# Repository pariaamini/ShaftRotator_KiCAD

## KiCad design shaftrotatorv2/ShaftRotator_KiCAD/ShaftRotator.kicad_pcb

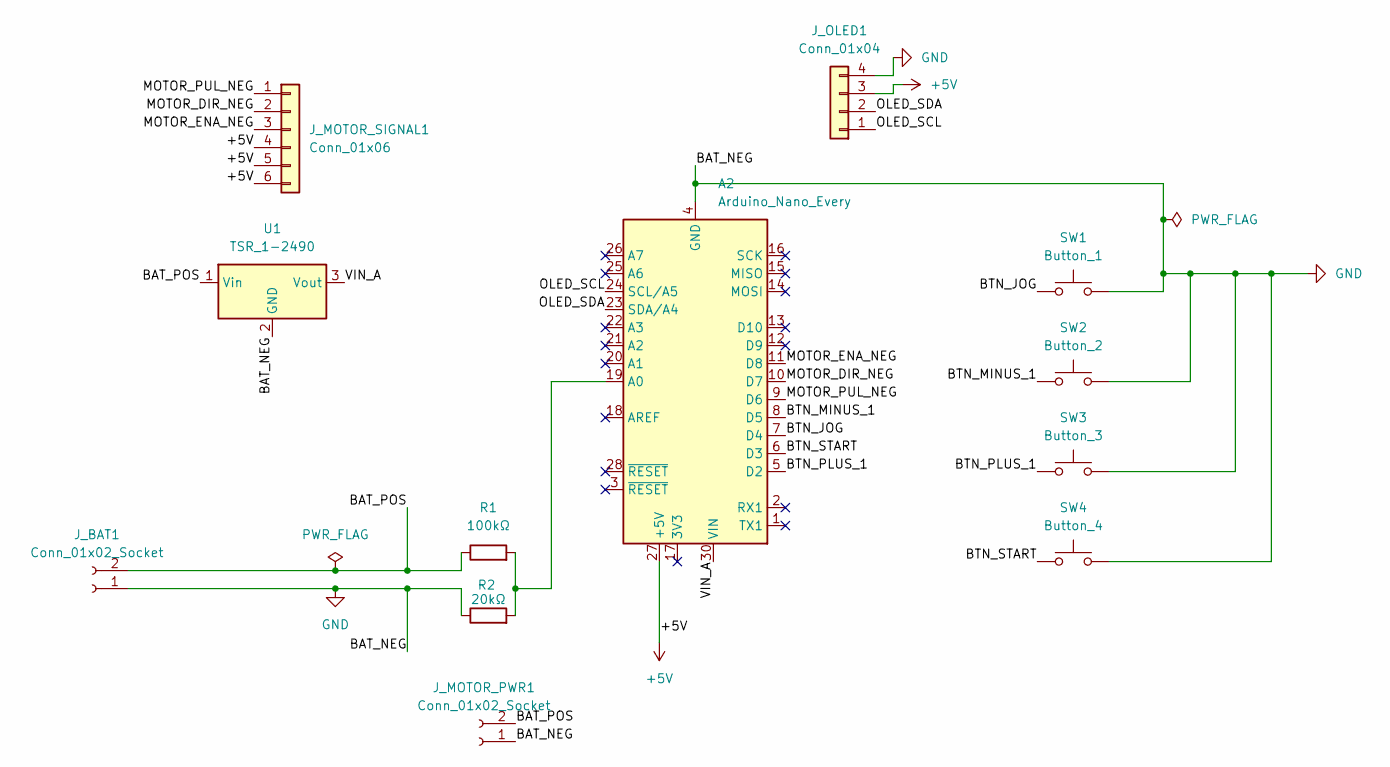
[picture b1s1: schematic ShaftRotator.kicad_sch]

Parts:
A2: Arduino_Nano_Every; Arduino_Nano
J_BAT1: Conn_01x02_Socket; JST_VH_B2P-VH_1x02_P3.96mm_Vertical
J_MOTOR_PWR1: Conn_01x02_Socket; JST_VH_B2P-VH_1x02_P3.96mm_Vertical
J_MOTOR_SIGNAL1: Conn_01x06; JST_PH_B6B-PH-K_1x06_P2.00mm_Vertical
J_OLED1: Conn_01x04; GROVE-HW4-2.0-90D
R1: 100kΩ; R_Axial_DIN0207_L6.3mm_D2.5mm_P10.16mm_Horizontal
R2: 20kΩ; R_Axial_DIN0207_L6.3mm_D2.5mm_P10.16mm_Horizontal
SW1: Button_1; SW_D6R90_F2_LFS
SW2: Button_2; SW_D6R90_F2_LFS
SW3: Button_3; SW_D6R90_F2_LFS
SW4: Button_4; SW_D6R90_F2_LFS
U1: TSR_1-2490; Converter_DCDC_TRACO_TSR-1_THT

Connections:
+5V: A2.27 (+5V), J_MOTOR_SIGNAL1.4, J_MOTOR_SIGNAL1.5, J_MOTOR_SIGNAL1.6, J_OLED1.3
/BAT_POS: J_BAT1.2, J_MOTOR_PWR1.2, R1.1, U1.1 (Vin)
/BTN_JOG: A2.7 (D4), SW1.1
/BTN_MINUS_1: A2.8 (D5), SW2.1
/BTN_PLUS_1: A2.5 (D2), SW3.1
/BTN_START: A2.6 (D3), SW4.1
/MOTOR_DIR_NEG: A2.10 (D7), J_MOTOR_SIGNAL1.2
/MOTOR_ENA_NEG: A2.11 (D8), J_MOTOR_SIGNAL1.3
/MOTOR_PUL_NEG: A2.9 (D6), J_MOTOR_SIGNAL1.1
/OLED_SCL: A2.24 (SCL/A5), J_OLED1.1
/OLED_SDA: A2.23 (SDA/A4), J_OLED1.2
/VIN_A: A2.30 (VIN), U1.3 (Vout)
GND: A2.4 (GND), A2.29 (GND), J_BAT1.1, J_MOTOR_PWR1.1, J_OLED1.4, R2.1, SW1.2, SW2.2, SW3.2, SW4.2, U1.2 (GND)
unnamed: A2.19 (A0), R1.2, R2.2

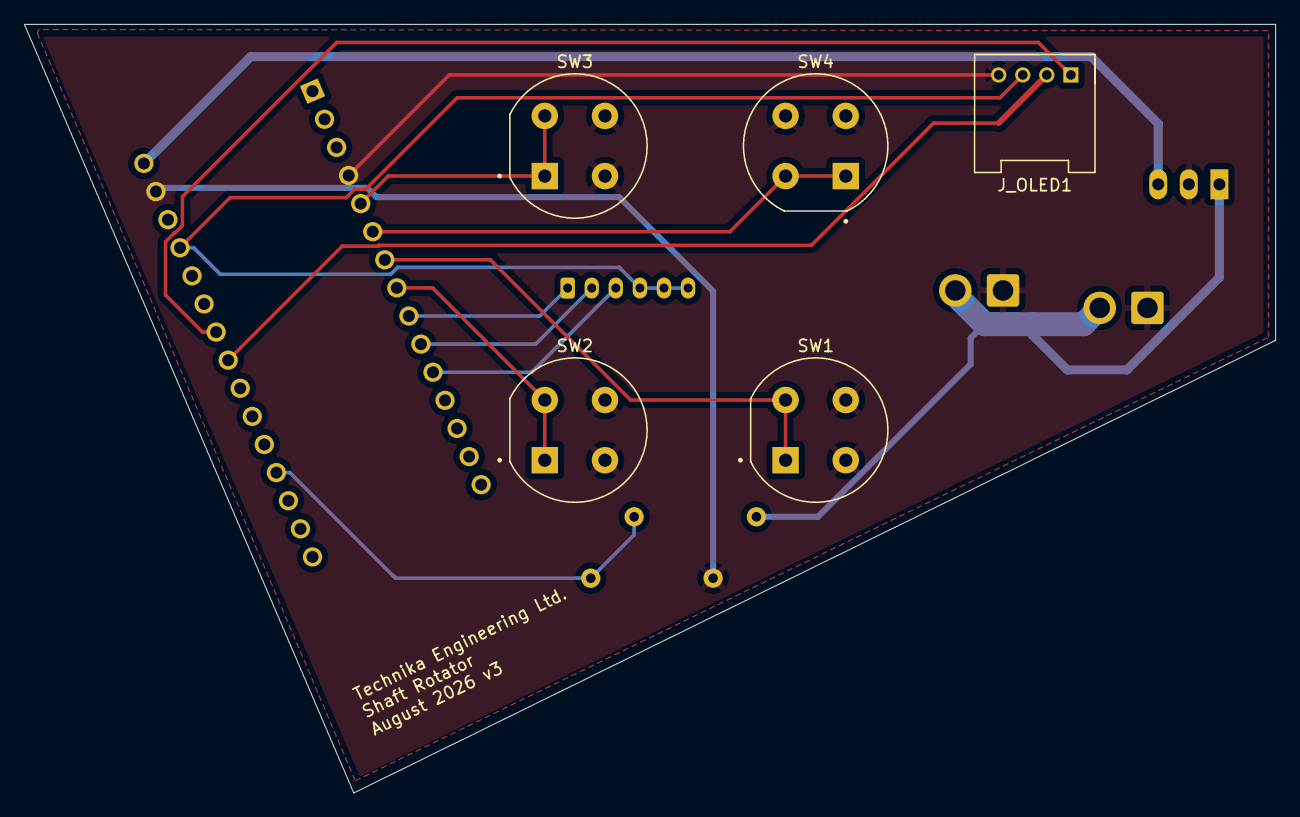
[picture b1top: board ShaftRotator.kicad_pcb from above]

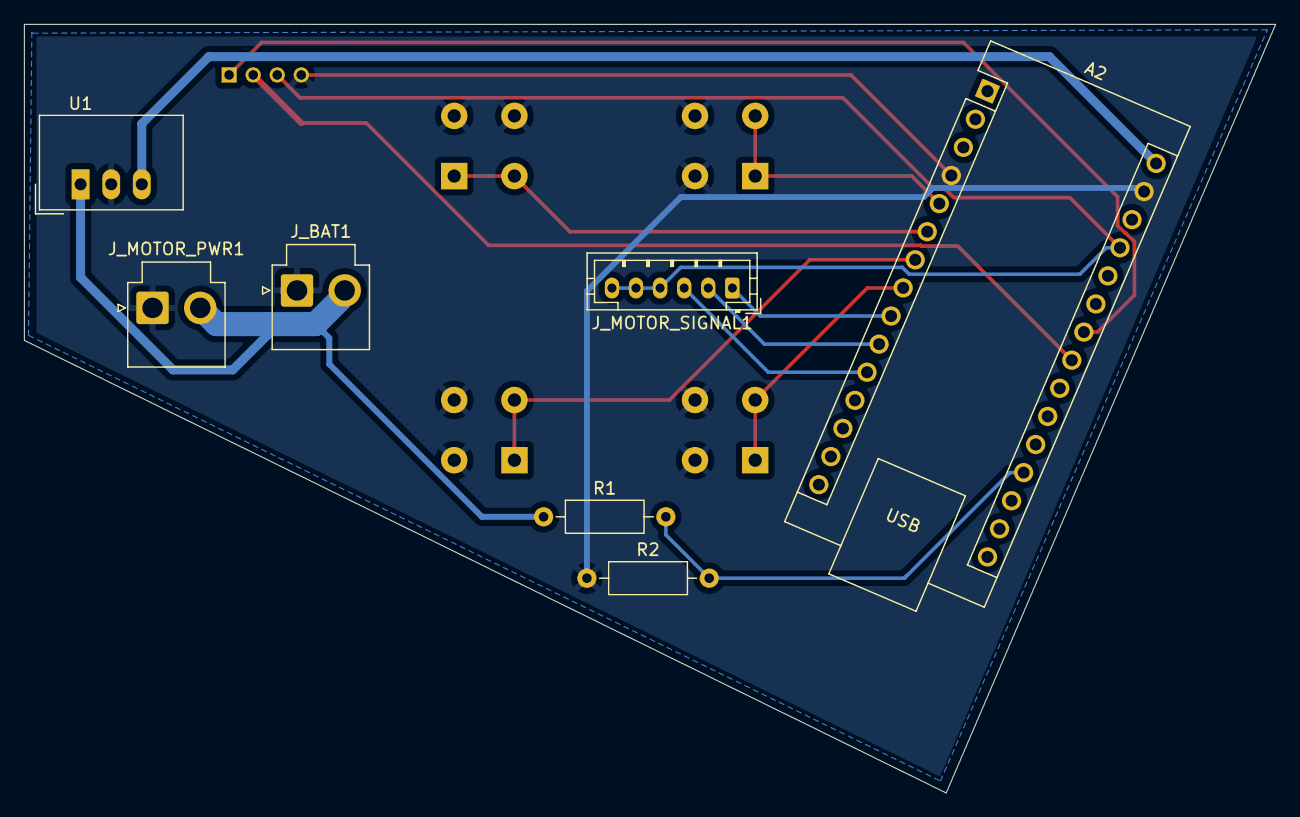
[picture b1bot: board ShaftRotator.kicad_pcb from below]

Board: 2 copper layers, 103.9 x 63.8 mm, 12 parts (7 on the bottom side), 14 nets.
